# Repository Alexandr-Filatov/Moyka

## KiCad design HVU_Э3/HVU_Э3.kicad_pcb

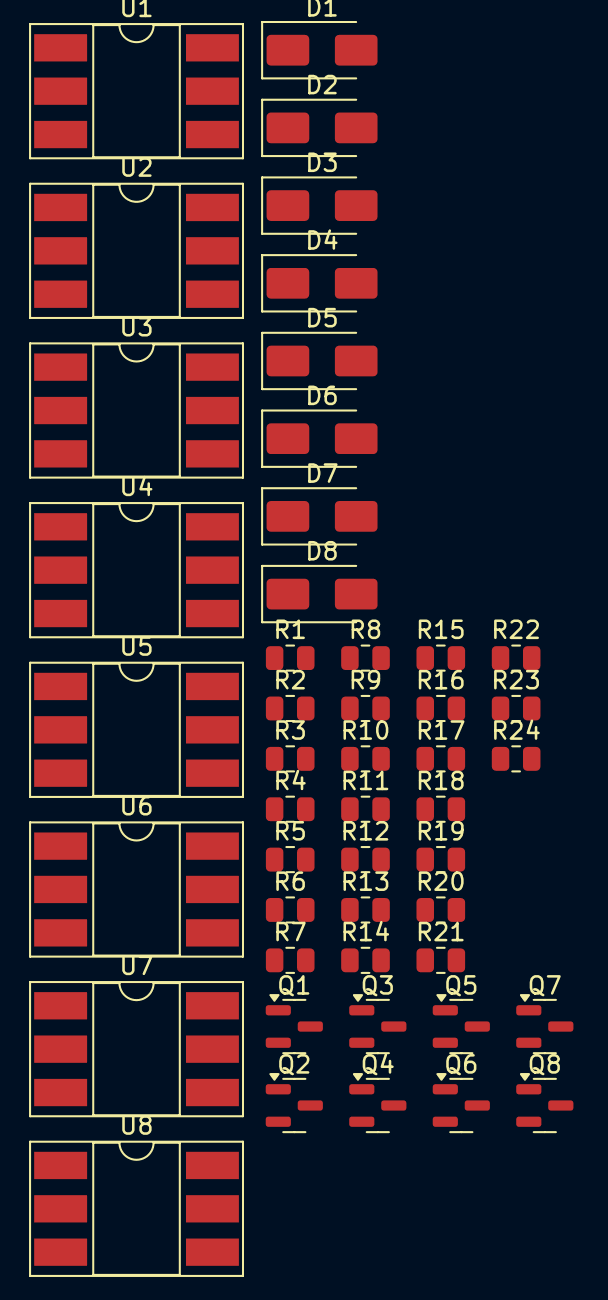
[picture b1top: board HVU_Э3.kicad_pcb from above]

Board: 2 copper layers, 48 parts (0 on the bottom side), 36 nets, no tracks yet.

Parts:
D1, D2, D3, D4, D5, D6, D7, D8: D; D_SMA
Q1, Q2, Q3, Q4, Q5, Q6, Q7, Q8: BC817; SOT-23
R1, R4, R7, R10, R13, R16, R19, R22: 220; R_0805_2012Metric
R2, R5, R8, R11, R14, R17, R20, R23: 4.7k; R_0805_2012Metric
R3, R6, R9, R12, R15, R18, R21, R24: 10K; R_0805_2012Metric
U1, U2, U3, U4, U5, U6, U7, U8: PVG612; DIP-6_W8.89mm_SMDSocket_LongPads

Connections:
AUX_Precharge_OUT: D6.1 (K), U6.4
AUX_Shunt_OUT: D5.1 (K), U5.4
Charge_OUT: D2.1 (K), U2.4
DCDC_Precharge_OUT: D8.1 (K), U8.4
DCDC_Shunt_OUT: D7.1 (K), U7.4
EVD80_Precharge_OUT: D4.1 (K), U4.4
EVD80_Shunt_OUT: D3.1 (K), U3.4
GND: Q1.2 (E), Q2.2 (E), Q3.2 (E), Q4.2 (E), Q5.2 (E), Q6.2 (E), Q7.2 (E), Q8.2 (E), R3.2, R6.2, R9.2, R12.2, R15.2, R18.2, R21.2, R24.2
GND_IN: D1.2 (A), D2.2 (A), D3.2 (A), D4.2 (A), D5.2 (A), D6.2 (A), D7.2 (A), D8.2 (A)
Hydrogen_OUT: D1.1 (K), U1.4
unnamed: Q1.1 (B), R2.2, R3.1
unnamed: Q1.3 (C), U1.2
unnamed: Q2.1 (B), R5.2, R6.1
unnamed: Q2.3 (C), U2.2
unnamed: Q3.1 (B), R8.2, R9.1
unnamed: Q3.3 (C), U3.2
unnamed: Q4.1 (B), R11.2, R12.1
unnamed: Q4.3 (C), U4.2
unnamed: Q5.1 (B), R14.2, R15.1
unnamed: Q5.3 (C), U5.2
unnamed: Q6.1 (B), R17.2, R18.1
unnamed: Q6.3 (C), U6.2
unnamed: Q7.1 (B), R20.2, R21.1
unnamed: Q7.3 (C), U7.2
unnamed: Q8.1 (B), R23.2, R24.1
unnamed: Q8.3 (C), U8.2
unnamed: R1.2, U1.1
unnamed: R4.2, U2.1
unnamed: R7.2, U3.1
unnamed: R10.2, U4.1
unnamed: R13.2, U5.1
unnamed: R16.2, U6.1
unnamed: R19.2, U7.1
unnamed: R22.2, U8.1
VDD_3V3: R1.1, R4.1, R7.1, R10.1, R13.1, R16.1, R19.1, R22.1
VIN: U1.6, U2.6, U3.6, U4.6, U5.6, U6.6, U7.6, U8.6

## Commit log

2024-08-08 Zero commit
2024-08-08 Поменял децимальники
2024-10-10 Поменял шрифты на схеме
